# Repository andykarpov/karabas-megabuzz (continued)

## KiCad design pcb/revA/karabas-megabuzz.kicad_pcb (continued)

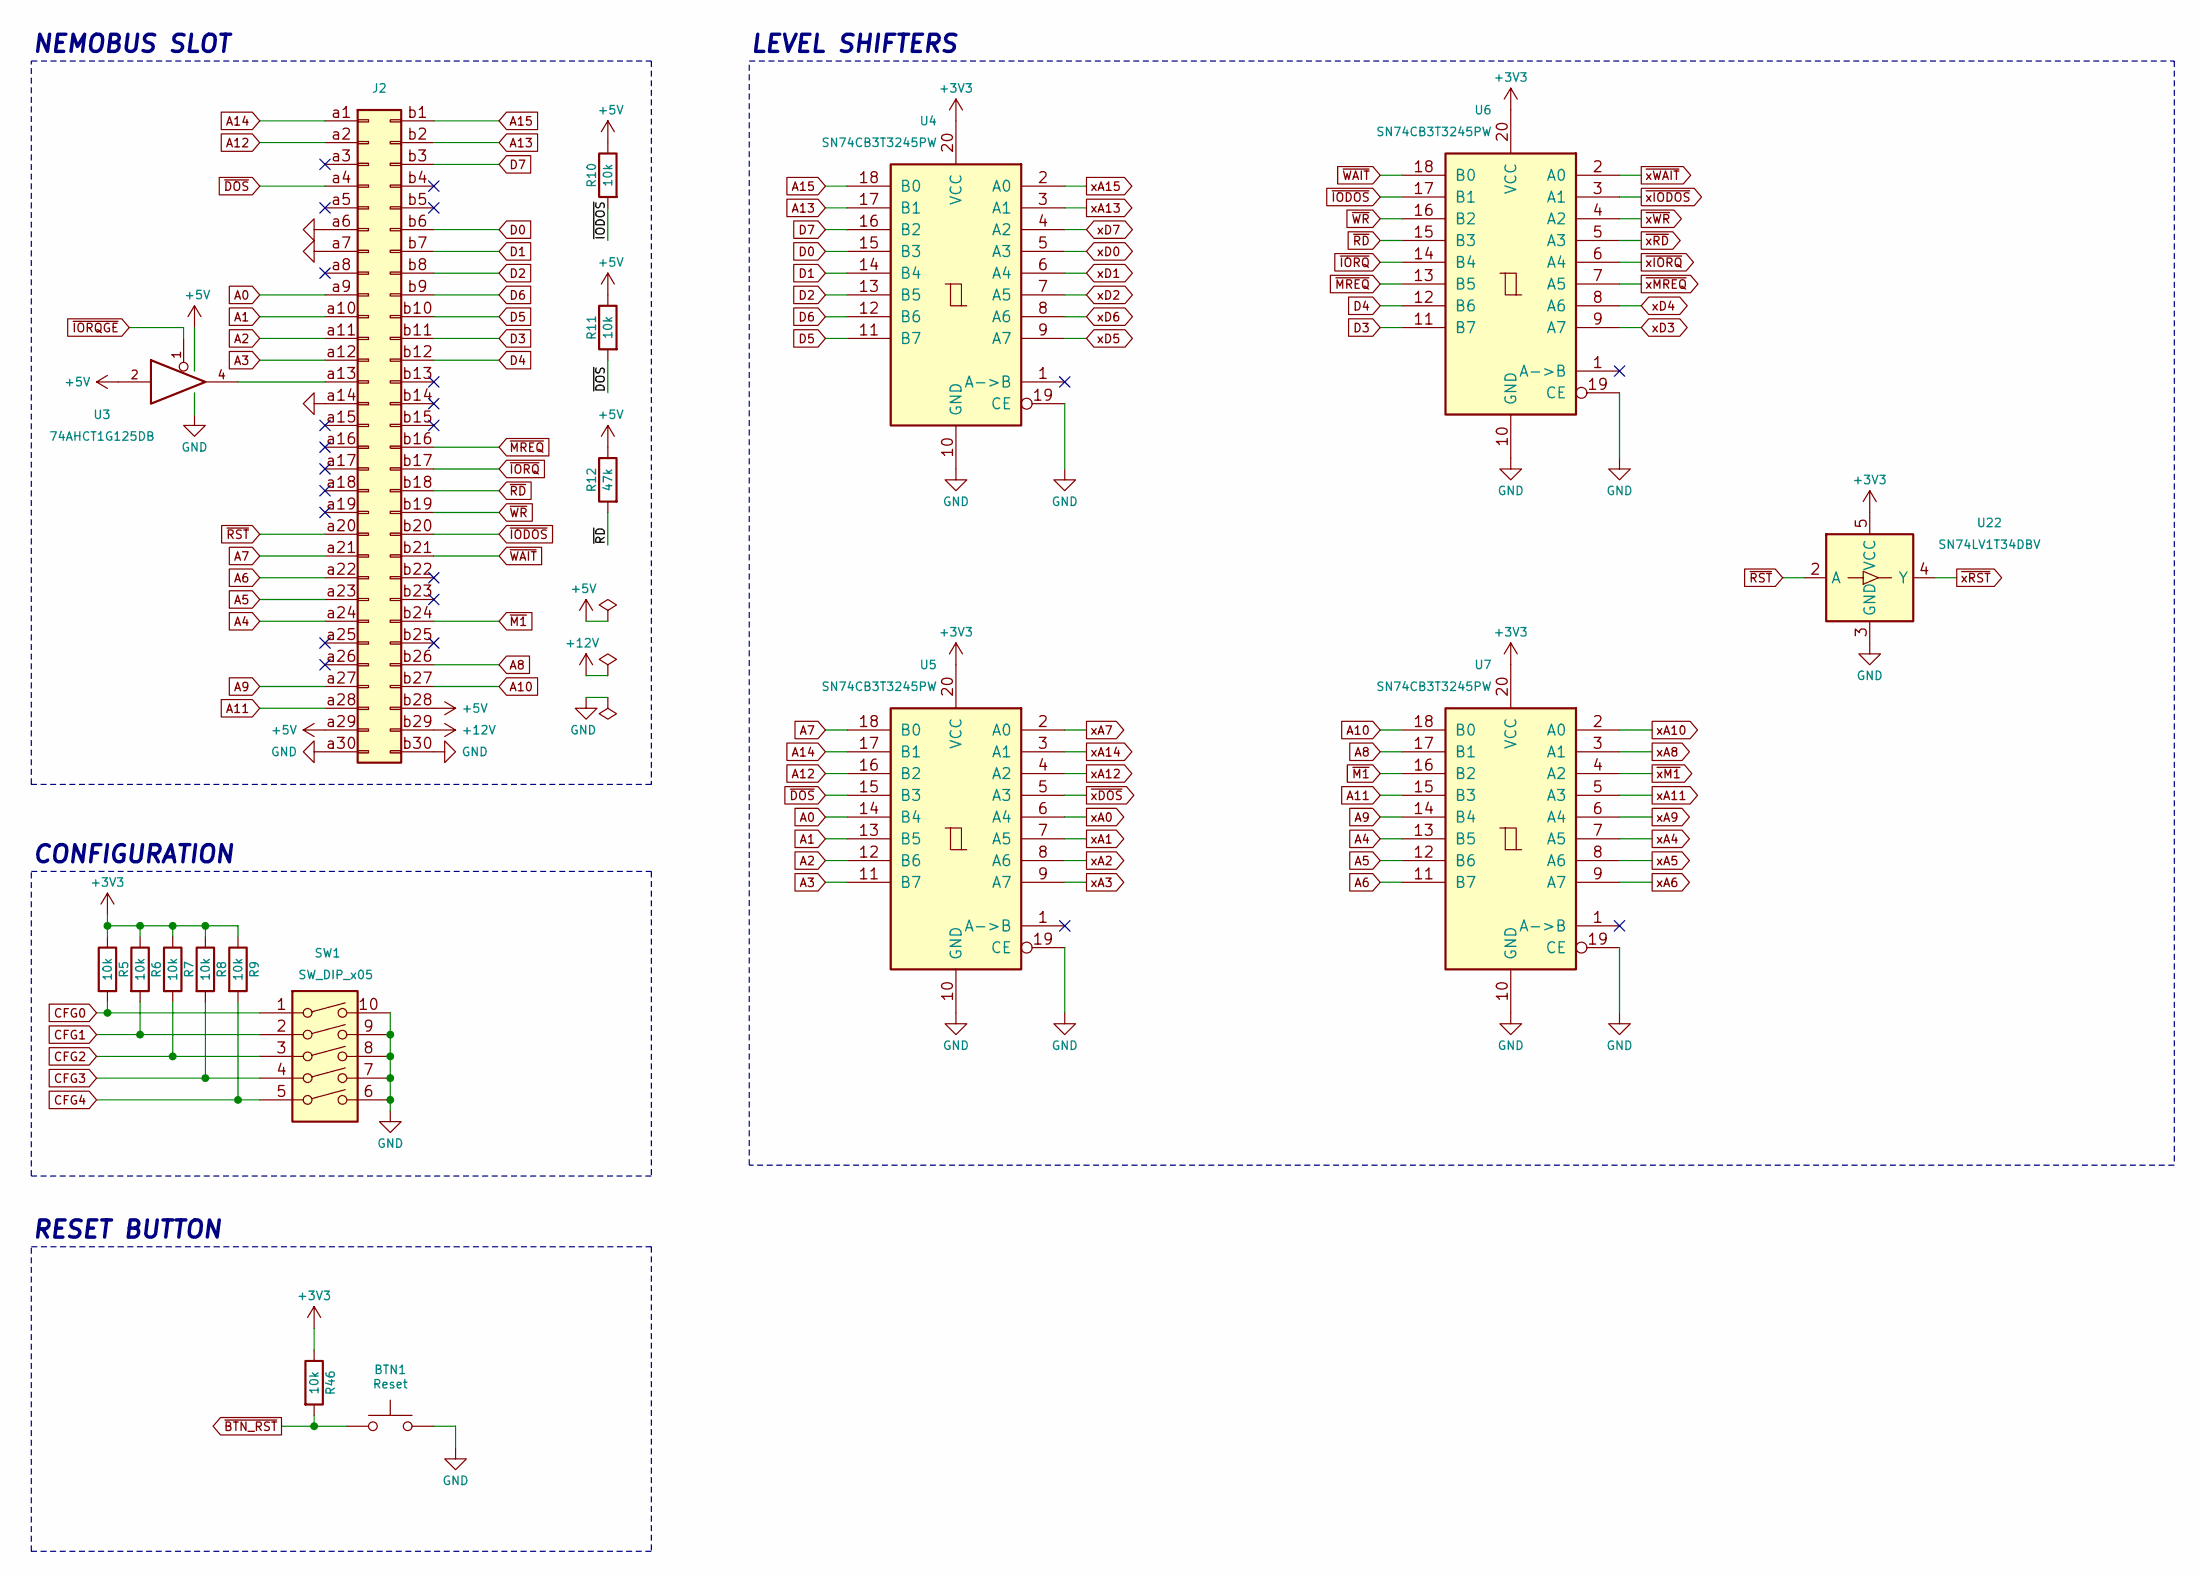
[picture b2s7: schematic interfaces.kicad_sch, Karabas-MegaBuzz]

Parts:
BTN1: Reset; SW_SPST_PTS810_handsoldering
J2: Conn_02x30_Row_Letter_First; ZX_NEMO_60_EDGE
R5, R6, R7, R8, R9, R10, R11, R46: 10k; R_0603_1608Metric_Pad0.98x0.95mm_HandSolder
R12: 47k; R_0603_1608Metric_Pad0.98x0.95mm_HandSolder
SW1: SW_DIP_x05; SW_DIP_SPSTx05_Slide_6.7x14.26mm_W7.62mm_P2.54mm_LowProfile
U3: 74AHCT1G125DB; SOT-23-5_HandSoldering
U4, U5, U6, U7: SN74CB3T3245PW; TSSOP-20_4.4x6.5mm_P0.65mm
U22: SN74LV1T34DBV; SOT-23-5_HandSoldering

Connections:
+3V3: R5.1, R6.1, R7.1, R8.1, R9.1, R46.1, U4.20 (VCC), U5.20 (VCC), U6.20 (VCC), U7.20 (VCC), U22.5 (VCC); also elsewhere on the board
+5V: J2.a29, J2.b28, R10.1, R11.1, R12.1, U3.2, U3.5 (VCC); also elsewhere on the board
+12V: J2.b29
A0: J2.a9, U5.14 (B4)
A1: J2.a10, U5.13 (B5)
A2: J2.a11, U5.12 (B6)
A3: J2.a12, U5.11 (B7)
A4: J2.a24, U7.13 (B5)
A5: J2.a23, U7.12 (B6)
A6: J2.a22, U7.11 (B7)
A7: J2.a21, U5.18 (B0)
A8: J2.b26, U7.17 (B1)
A9: J2.a27, U7.14 (B4)
A10: J2.b27, U7.18 (B0)
A11: J2.a28, U7.15 (B3)
A12: J2.a2, U5.16 (B2)
A13: J2.b2, U4.17 (B1)
A14: J2.a1, U5.17 (B1)
A15: J2.b1, U4.18 (B0)
CFG0: R5.2, SW1.1; also elsewhere on the board
CFG1: R6.2, SW1.2; also elsewhere on the board
CFG2: R7.2, SW1.3; also elsewhere on the board
CFG3: R8.2, SW1.4; also elsewhere on the board
CFG4: R9.2, SW1.5; also elsewhere on the board
D0: J2.b6, U4.15 (B3); also elsewhere on the board
D1: J2.b7, U4.14 (B4); also elsewhere on the board
D2: J2.b8, U4.13 (B5); also elsewhere on the board
D3: J2.b11, U6.11 (B7); also elsewhere on the board
D4: J2.b12, U6.12 (B6); also elsewhere on the board
D5: J2.b10, U4.11 (B7); also elsewhere on the board
D6: J2.b9, U4.12 (B6); also elsewhere on the board
D7: J2.b3, U4.16 (B2); also elsewhere on the board
GND: BTN1.2, J2.a6, J2.a7, J2.a14, J2.a30, J2.b30, SW1.6, SW1.7, SW1.8, SW1.9, SW1.10, U3.3 (GND), U4.10 (GND), U4.19 (CE), U5.10 (GND), U5.19 (CE), U6.10 (GND), U6.19 (CE), U7.10 (GND), U7.19 (CE), U22.3 (GND); also elsewhere on the board
unnamed: J2.a13, U3.4
xA0: U5.6 (A4); also elsewhere on the board
xA1: U5.7 (A5); also elsewhere on the board
xA2: U5.8 (A6); also elsewhere on the board
xA3: U5.9 (A7); also elsewhere on the board
xA4: U7.7 (A5); also elsewhere on the board
xA5: U7.8 (A6); also elsewhere on the board
xA6: U7.9 (A7); also elsewhere on the board
xA7: U5.2 (A0); also elsewhere on the board
xA8: U7.3 (A1); also elsewhere on the board
xA9: U7.6 (A4); also elsewhere on the board
xA10: U7.2 (A0); also elsewhere on the board
xA11: U7.5 (A3); also elsewhere on the board
xA12: U5.4 (A2); also elsewhere on the board
xA13: U4.3 (A1); also elsewhere on the board
xA14: U5.3 (A1); also elsewhere on the board
xA15: U4.2 (A0); also elsewhere on the board
xD0: U4.5 (A3); also elsewhere on the board
xD1: U4.6 (A4); also elsewhere on the board
xD2: U4.7 (A5); also elsewhere on the board
xD3: U6.9 (A7); also elsewhere on the board
xD4: U6.8 (A6); also elsewhere on the board
xD5: U4.9 (A7); also elsewhere on the board
xD6: U4.8 (A6); also elsewhere on the board
xD7: U4.4 (A2); also elsewhere on the board
~BTN_RST: BTN1.1, R46.2; also elsewhere on the board
~DOS: J2.a4, R11.2, U5.15 (B3)
~IODOS: J2.b20, R10.2, U6.17 (B1)
~IORQGE: U3.1; also elsewhere on the board
~IORQ: J2.b17, U6.14 (B4)
~M1: J2.b24, U7.16 (B2)
~MREQ: J2.b16, U6.13 (B5)
~RD: J2.b18, R12.2, U6.15 (B3); also elsewhere on the board
~RST: J2.a20, U22.2 (A)
~WAIT: J2.b21, U6.18 (B0)
~WR: J2.b19, U6.16 (B2); also elsewhere on the board
~xDOS: U5.5 (A3); also elsewhere on the board
~xIODOS: U6.3 (A1); also elsewhere on the board
~xIORQ: U6.6 (A4); also elsewhere on the board
~xM1: U7.4 (A2); also elsewhere on the board
~xMREQ: U6.7 (A5); also elsewhere on the board
~xRD: U6.5 (A3); also elsewhere on the board
~xRST: U22.4 (Y); also elsewhere on the board
~xWAIT: U6.2 (A0); also elsewhere on the board
~xWR: U6.4 (A2); also elsewhere on the board

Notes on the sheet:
CONFIGURATION
LEVEL SHIFTERS
NEMOBUS SLOT
RESET BUTTON

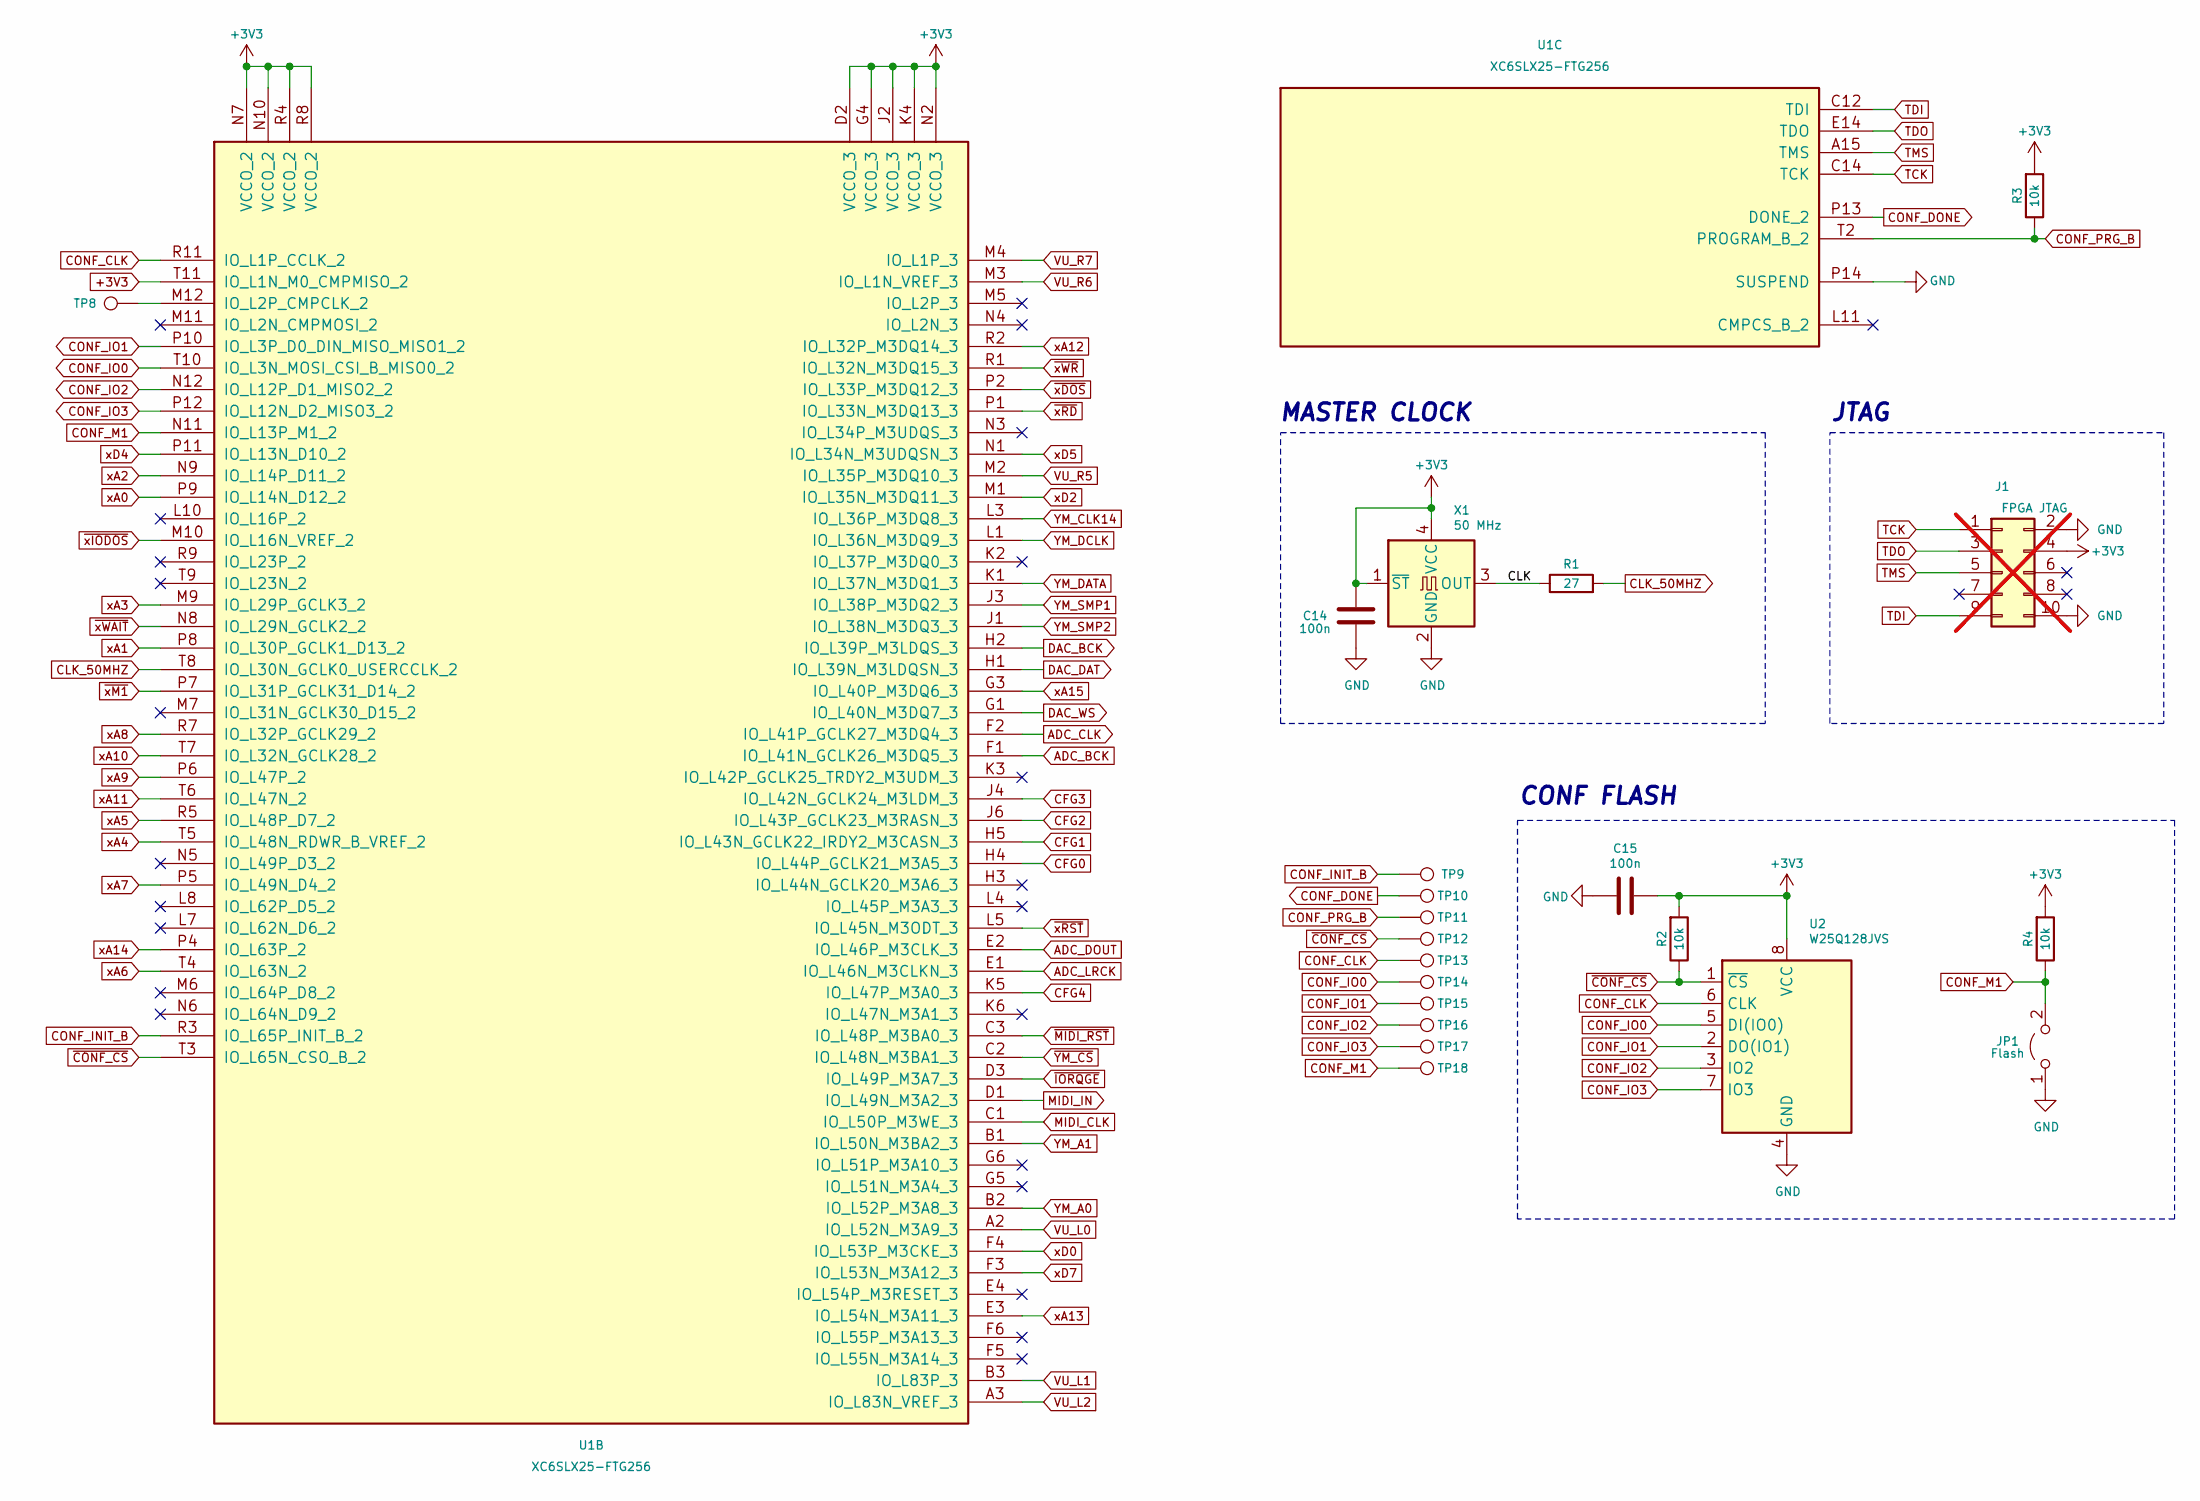
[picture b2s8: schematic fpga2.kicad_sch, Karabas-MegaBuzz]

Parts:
C14, C15: 100n; C_0603_1608Metric_Pad1.08x0.95mm_HandSolder
J1: FPGA JTAG; PinHeader_2x05_P2.54mm_Vertical; not fitted
JP1: Flash; SolderJumper-2_P1.3mm_Bridged_RoundedPad1.0x1.5mm
R1: 27; R_0603_1608Metric_Pad0.98x0.95mm_HandSolder
R2, R3, R4: 10k; R_0603_1608Metric_Pad0.98x0.95mm_HandSolder
TP8, TP9, TP10, TP11, TP12, TP13, TP14, TP15, TP16, TP17, TP18: TestPoint; TestPoint_Pad_D1.5mm
U1: XC6SLX25-FTG256; BGA-256_17.0x17.0mm_Layout16x16_P1.0mm_Ball0.5mm_Pad0.4mm_N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
U2: W25Q128JVS; SOIC-8_5.3x5.3mm_P1.27mm
X1: 50 MHz; Oscillator_SMD_SeikoEpson_SG8002CA-4Pin_7.0x5.0mm

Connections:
+3V3: C14.1, C15.1, J1.4, R2.2, R3.2, R4.2, U1.D2 (VCCO_3), U1.G4 (VCCO_3), U1.J2 (VCCO_3), U1.K4 (VCCO_3), U1.N2 (VCCO_3), U1.N7 (VCCO_2), U1.N10 (VCCO_2), U1.R4 (VCCO_2), U1.R8 (VCCO_2), U1.T11 (IO_L1N_M0_CMPMISO_2), U2.8 (VCC), X1.1 (~ST), X1.4 (VCC); also elsewhere on the board
/FPGA2/CLK: R1.1, X1.3 (OUT)
ADC_BCK: U1.F1 (IO_L41N_GCLK26_M3DQ5_3); also elsewhere on the board
ADC_CLK: U1.F2 (IO_L41P_GCLK27_M3DQ4_3); also elsewhere on the board
ADC_DOUT: U1.E2 (IO_L46P_M3CLK_3); also elsewhere on the board
ADC_LRCK: U1.E1 (IO_L46N_M3CLKN_3); also elsewhere on the board
CFG0: U1.H4 (IO_L44P_GCLK21_M3A5_3); also elsewhere on the board
CFG1: U1.H5 (IO_L43N_GCLK22_IRDY2_M3CASN_3); also elsewhere on the board
CFG2: U1.J6 (IO_L43P_GCLK23_M3RASN_3); also elsewhere on the board
CFG3: U1.J4 (IO_L42N_GCLK24_M3LDM_3); also elsewhere on the board
CFG4: U1.K5 (IO_L47P_M3A0_3); also elsewhere on the board
CLK_50MHZ: R1.2, U1.T8 (IO_L30N_GCLK0_USERCCLK_2)
CONF_CLK: TP13.1 (1_1), U1.R11 (IO_L1P_CCLK_2), U2.6 (CLK)
CONF_DONE: TP10.1 (1_1), U1.P13 (DONE_2)
CONF_INIT_B: TP9.1 (1_1), U1.R3 (IO_L65P_INIT_B_2)
CONF_IO0: TP14.1 (1_1), U1.T10 (IO_L3N_MOSI_CSI_B_MISO0_2), U2.5 (DI(IO0))
CONF_IO1: TP15.1 (1_1), U1.P10 (IO_L3P_D0_DIN_MISO_MISO1_2), U2.2 (DO(IO1))
CONF_IO2: TP16.1 (1_1), U1.N12 (IO_L12P_D1_MISO2_2), U2.3 (IO2)
CONF_IO3: TP17.1 (1_1), U1.P12 (IO_L12N_D2_MISO3_2), U2.7 (IO3)
CONF_M1: JP1.2 (B), R4.1, TP18.1 (1_1), U1.N11 (IO_L13P_M1_2)
CONF_PRG_B: R3.1, TP11.1 (1_1), U1.T2 (PROGRAM_B_2)
DAC_BCK: U1.H2 (IO_L39P_M3LDQS_3); also elsewhere on the board
DAC_DAT: U1.H1 (IO_L39N_M3LDQSN_3); also elsewhere on the board
DAC_WS: U1.G1 (IO_L40N_M3DQ7_3); also elsewhere on the board
GND: C14.2, C15.2, J1.2, J1.10, JP1.1 (A), U1.P14 (SUSPEND), U2.4 (GND), X1.2 (GND); also elsewhere on the board
MIDI_CLK: U1.C1 (IO_L50P_M3WE_3); also elsewhere on the board
MIDI_IN: U1.D1 (IO_L49N_M3A2_3); also elsewhere on the board
unnamed: TP8.1 (1_1), U1.M12 (IO_L2P_CMPCLK_2)
TCK: J1.1, U1.C14 (TCK)
TDI: J1.9, U1.C12 (TDI)
TDO: J1.3, U1.E14 (TDO)
TMS: J1.5, U1.A15 (TMS)
VU_L0: U1.A2 (IO_L52N_M3A9_3); also elsewhere on the board
VU_L1: U1.B3 (IO_L83P_3); also elsewhere on the board
VU_L2: U1.A3 (IO_L83N_VREF_3); also elsewhere on the board
VU_R5: U1.M2 (IO_L35P_M3DQ10_3); also elsewhere on the board
VU_R6: U1.M3 (IO_L1N_VREF_3); also elsewhere on the board
VU_R7: U1.M4 (IO_L1P_3); also elsewhere on the board
YM_A0: U1.B2 (IO_L52P_M3A8_3); also elsewhere on the board
YM_A1: U1.B1 (IO_L50N_M3BA2_3); also elsewhere on the board
YM_CLK14: U1.L3 (IO_L36P_M3DQ8_3); also elsewhere on the board
YM_DATA: U1.K1 (IO_L37N_M3DQ1_3); also elsewhere on the board
YM_DCLK: U1.L1 (IO_L36N_M3DQ9_3); also elsewhere on the board
YM_SMP1: U1.J3 (IO_L38P_M3DQ2_3); also elsewhere on the board
YM_SMP2: U1.J1 (IO_L38N_M3DQ3_3); also elsewhere on the board
xA0: U1.P9 (IO_L14N_D12_2); also elsewhere on the board
xA1: U1.P8 (IO_L30P_GCLK1_D13_2); also elsewhere on the board
xA2: U1.N9 (IO_L14P_D11_2); also elsewhere on the board
xA3: U1.M9 (IO_L29P_GCLK3_2); also elsewhere on the board
xA4: U1.T5 (IO_L48N_RDWR_B_VREF_2); also elsewhere on the board
xA5: U1.R5 (IO_L48P_D7_2); also elsewhere on the board
xA6: U1.T4 (IO_L63N_2); also elsewhere on the board
xA7: U1.P5 (IO_L49N_D4_2); also elsewhere on the board
xA8: U1.R7 (IO_L32P_GCLK29_2); also elsewhere on the board
xA9: U1.P6 (IO_L47P_2); also elsewhere on the board
xA10: U1.T7 (IO_L32N_GCLK28_2); also elsewhere on the board
xA11: U1.T6 (IO_L47N_2); also elsewhere on the board
xA12: U1.R2 (IO_L32P_M3DQ14_3); also elsewhere on the board
xA13: U1.E3 (IO_L54N_M3A11_3); also elsewhere on the board
xA14: U1.P4 (IO_L63P_2); also elsewhere on the board
xA15: U1.G3 (IO_L40P_M3DQ6_3); also elsewhere on the board
xD0: U1.F4 (IO_L53P_M3CKE_3); also elsewhere on the board
xD2: U1.M1 (IO_L35N_M3DQ11_3); also elsewhere on the board
xD4: U1.P11 (IO_L13N_D10_2); also elsewhere on the board
xD5: U1.N1 (IO_L34N_M3UDQSN_3); also elsewhere on the board
xD7: U1.F3 (IO_L53N_M3A12_3); also elsewhere on the board
~CONF_CS: R2.1, TP12.1 (1_1), U1.T3 (IO_L65N_CSO_B_2), U2.1 (~CS)
~IORQGE: U1.D3 (IO_L49P_M3A7_3); also elsewhere on the board
~MIDI_RST: U1.C3 (IO_L48P_M3BA0_3); also elsewhere on the board
~YM_CS: U1.C2 (IO_L48N_M3BA1_3); also elsewhere on the board
~xDOS: U1.P2 (IO_L33P_M3DQ12_3); also elsewhere on the board
~xIODOS: U1.M10 (IO_L16N_VREF_2); also elsewhere on the board
~xM1: U1.P7 (IO_L31P_GCLK31_D14_2); also elsewhere on the board
~xRD: U1.P1 (IO_L33N_M3DQ13_3); also elsewhere on the board
~xRST: U1.L5 (IO_L45N_M3ODT_3); also elsewhere on the board
~xWAIT: U1.N8 (IO_L29N_GCLK2_2); also elsewhere on the board
~xWR: U1.R1 (IO_L32N_M3DQ15_3); also elsewhere on the board

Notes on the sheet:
CONF FLASH
JTAG
MASTER CLOCK

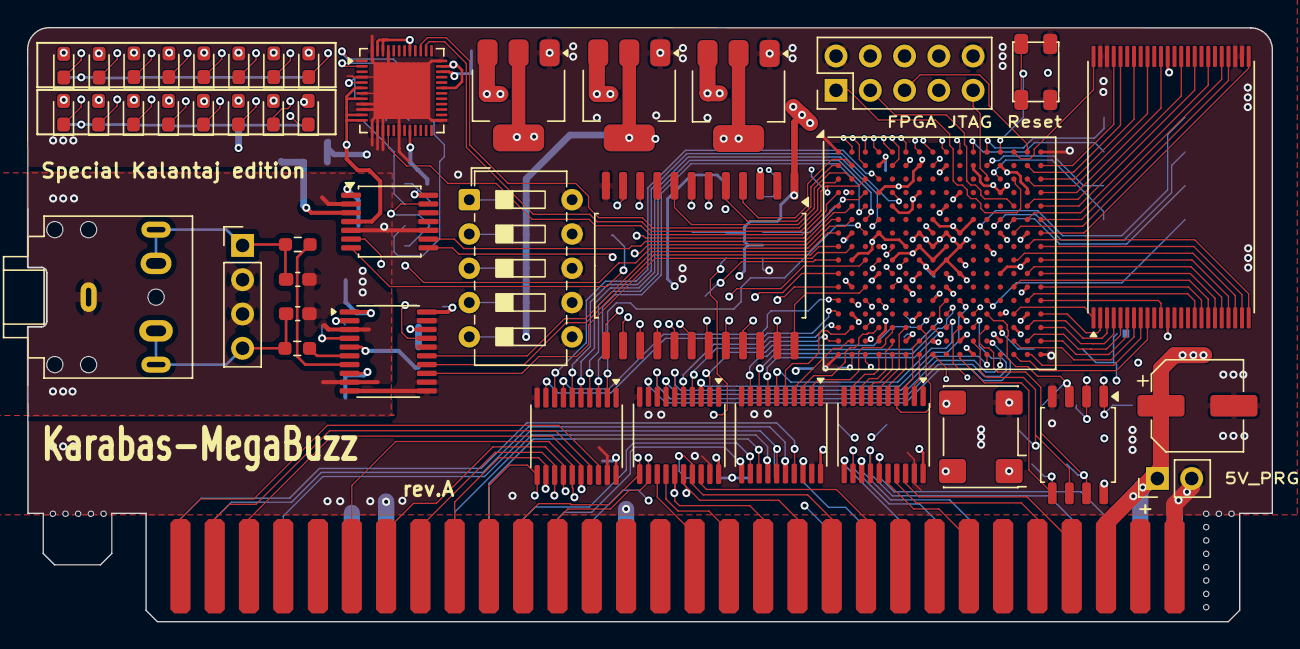
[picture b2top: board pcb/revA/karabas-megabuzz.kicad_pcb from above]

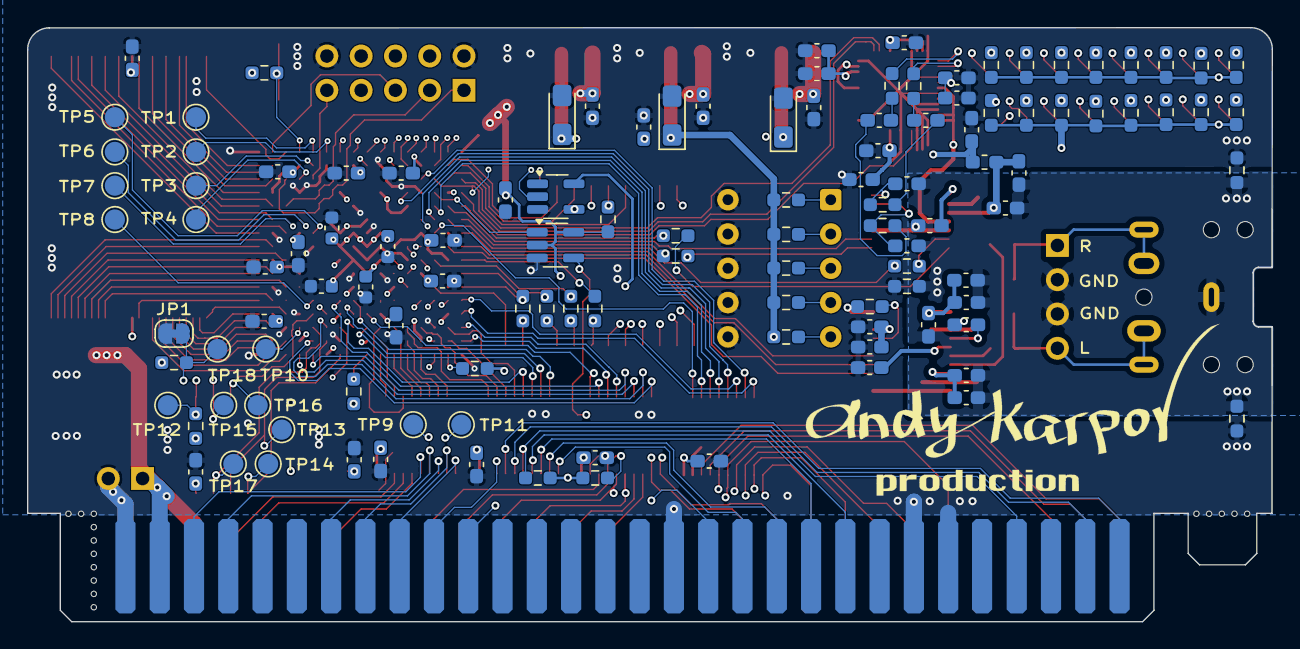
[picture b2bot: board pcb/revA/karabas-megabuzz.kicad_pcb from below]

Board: 4 copper layers, 92.2 x 44.0 mm, 162 parts (119 on the bottom side), 213 nets.

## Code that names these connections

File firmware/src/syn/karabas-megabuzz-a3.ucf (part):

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# MIDI
NET "midi_tx"             LOC="D1"    | IOSTANDARD = LVCMOS33;
NET "midi_reset_n"        LOC="C3"    | IOSTANDARD = LVCMOS33;
NET "midi_clk"            LOC="C1"    | IOSTANDARD = LVCMOS33;

# GS SRAM
NET "mem_a<0>"            LOC="G16"   | IOSTANDARD = LVCMOS33 | DRIVE = 4 | SLEW = "FAST" | NODELAY;
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NET "opl3_dclk"           LOC="L1"    | IOSTANDARD = LVCMOS33;

# ADC (i2s)
NET "adc_clk"             LOC="F2"    | IOSTANDARD = LVCMOS33;
NET "adc_bck"             LOC="F1"    | IOSTANDARD = LVCMOS33;
NET "adc_lrck"            LOC="E1"    | IOSTANDARD = LVCMOS33;
NET "adc_dat"             LOC="E2"    | IOSTANDARD = LVCMOS33;

# DAC (i2s)
NET "dac_bck"             LOC="H2"    | IOSTANDARD = LVCMOS33;
NET "dac_ws"              LOC="G1"    | IOSTANDARD = LVCMOS33;
NET "dac_dat"             LOC="H1"    | IOSTANDARD = LVCMOS33;

# SPI FLASH
NET "flash_cs_n"          LOC="T3"   | IOSTANDARD = LVCMOS33; # /CONF_CS
NET "flash_miso"          LOC="P10"  | IOSTANDARD = LVCMOS33; # CONF_IO1
NET "flash_mosi"          LOC="T10"  | IOSTANDARD = LVCMOS33; # CONF_IO0
NET "flash_sck"           LOC="R11"  | IOSTANDARD = LVCMOS33; # CONF_CLK
NET "flash_wp_n"          LOC="N12"  | IOSTANDARD = LVCMOS33; # CONF_IO2
NET "flash_hold_n"        LOC="P12"  | IOSTANDARD = LVCMOS33; # CONF_IO3

# PSRAM
NET "psram_cs_n"          LOC="M13"  | IOSTANDARD = LVCMOS33;

# SD CARD
NET "sd_cs_n"             LOC="F14"  | IOSTANDARD = LVCMOS33 | PULLUP;
NET "sd_di"               LOC="F13"  | IOSTANDARD = LVCMOS33;
NET "sd_do"               LOC="B14"  | IOSTANDARD = LVCMOS33 | PULLUP;
NET "sd_clk"              LOC="B12"  | IOSTANDARD = LVCMOS33;
NET "sd_det_n"            LOC="A11"  | IOSTANDARD = LVCMOS33 | PULLUP;

# VU Meter
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NET "led_meter_r<7>"      LOC="M4"   | IOSTANDARD = LVCMOS33 | DRIVE = 8;

# MMC LED
NET "led1"                LOC="D6"   | IOSTANDARD = LVCMOS33 | DRIVE = 8;

# TEST Points
NET "tp<1>"               LOC="M12"  | IOSTANDARD = LVCMOS33 | PULLUP;
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NET "scl"                 LOC="L7"   | IOSTANDARD = LVCMOS33;

# vs1053a
NET "vs_clk"              LOC="F7"   | IOSTANDARD = LVCMOS33 | SLEW = FAST;
NET "vs_reset_n"          LOC="L10"  | IOSTANDARD = LVCMOS33 | SLEW = SLOW;
NET "vs_cs_n"             LOC="L12"  | IOSTANDARD = LVCMOS33 | SLEW = SLOW;
NET "vs_dcs_n"            LOC="E8"   | IOSTANDARD = LVCMOS33 | SLEW = SLOW;
NET "vs_dreq"             LOC="D8"   | IOSTANDARD = LVCMOS33 | PULLUP;
NET "vs_mosi"             LOC="P2"   | IOSTANDARD = LVCMOS33 | SLEW = FAST;
NET "vs_miso"             LOC="N3"   | IOSTANDARD = LVCMOS33 | PULLUP;
NET "vs_sclk"             LOC="K2"   | IOSTANDARD = LVCMOS33 | SLEW = FAST;


# Timings
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
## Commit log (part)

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2026-04-19 Initial firmware
2026-04-19 git ignore
2026-04-19 updated gitignore
2026-04-19 removed backups
2026-04-19 Firmware WIP
2026-04-20 codestyle fixes
2026-04-20 cleanup
2026-04-20 Refactoring: project renamed
2026-04-20 Makefile to generate SVF to use via urJtag
2026-04-20 Prepared docs
2026-04-20 updated renders
2026-04-20 Updated gerbers to min 0.2/0.45 vias, firmware build for xc6slx16
2026-05-12 Added makefile via openFPGALoader
2026-05-12 gs test
2026-05-12 New SAA1099 module with cen for 8mhz
2026-05-12 Added falling dots in vu meter
2026-05-12 removed history
2026-05-12 project file update
2026-05-12 Refactored VU meter
2026-05-12 Split project into slx16/slx25 targets
2026-05-12 bugfix
2026-05-12 Added How-to
2026-05-23 midi tx sensor to disable adc out when no stream so far
2026-05-23 Almost working solution
2026-05-23 Fixed opl3 capture
2026-05-23 Update for slx25
2026-05-23 Default OPL3 to ON
2026-05-23 Added samplerate resampler
2026-05-23 Renamed opl3_resample to audio_resample
2026-05-23 Added resampler to 25k project
2026-05-23 updated 25k project
2026-05-23 Changed resample to actual output samplerate
2026-05-23 build for lx25
2026-05-26 Added bit files
2026-05-26 Updated workdir
2026-05-26 latest build
2026-05-26 bit update for lx25
2026-05-26 Fixed 8MHz cen generation
2026-05-26 slx25 release
2026-05-26 Fixed soundrive and covox
2026-05-26 Added initial reset
2026-05-27 revA1 WIP
2026-05-27 Added TP. Added /reset on TP1 for OPL3 hotfix
2026-05-27 Build for slx25
2026-05-27 Added TP logic to control VU direction and features
2026-05-27 Updated howto
2026-05-27 Added openFPGALoader spiOverJtag bitstreams for slx25
2026-05-27 Added resetter module (rst pulse ~3uS)
2026-05-27 ERRATA
2026-05-29 revA1, WIP
2026-05-29 revA1
2026-05-29 Project files for revA1
2026-05-29 Latest PCB changes
2026-05-29 ibom with tracks / zones
2026-05-29 PCB changelog
2026-05-29 Small improvements to the revA1
2026-06-02 Updated revA - rerouted OPL3 reset to /MIDI_RST
2026-06-04 Removed polygons under BGA chip on F.Cu layer
2026-06-06 Updated ERRATA
2026-06-07 Fixed missing LED1 connection, new revA1 release
2026-06-07 revB initial commit
2026-06-07 Updated revA (cosmetic changes)
2026-06-07 Added revB project files, actual 3d pcb screenshots
2026-06-07 Added test map
2026-06-14 Removed A1, B revisions from released files
2026-06-14 Reset signal quite longer. clock for OPL3 always propagated. Added missing led1
2026-06-14 Fixed VU direction
2026-06-15 Working ZC
2026-06-15 ESXDOS rom
2026-06-15 Added SD_DO pullup
2026-06-15 Fixed bus nmi out
2026-06-16 Fixed ROM block signal: swapped CSR / RDR
2026-06-16 Current Divmmc WIP
2026-06-16 Added zx rom, fixed divmmc port decoding
2026-06-16 Fixed A1 Schematics / PCB with RDR + BLK signals
2026-06-16 Fixed divmmc by areset
2026-06-17 SRAM arbiter. WIP
2026-06-17 Added wait cycles to CPU and GS
2026-06-17 Working 64kb divmmc + GS rom via flash loader
2026-06-17 removed zc_busy
2026-06-17 Project file update for 25k fpga
2026-06-17 Build files for 25k
2026-06-17 Fixed project for revA 16k
2026-06-17 Fixed project for revA 25k
2026-06-17 Added synth macros HW_A1
2026-06-17 DivMMC + ZC for revA1 (#1)
    * Current Divmmc WIP
    * Added zx rom, fixed divmmc port decoding
    * Fixed A1 Schematics / PCB with RDR + BLK signals
    * Fixed divmmc by areset
    * WIP
    * Working 64kb divmmc + GS rom via flash loader
2026-06-17 Docs, gerbers, ibom for Rev.A1
2026-06-18 Divmmc clock improvements
2026-06-18 Updated 25k build
2026-06-20 Updated sd signals
2026-06-20 25k a1 build
2026-06-21 pcb revA2
2026-06-21 Added readme
2026-06-21 revA2 updates
2026-06-21 A2 initial support
2026-06-21 A2 initial support for 25k
